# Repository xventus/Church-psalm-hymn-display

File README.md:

# Church psalm hymn display, display unit

Project for displaying hymn numbers and lyrics. This is the latest version and cheaper variant of the original FPGA VGA version. Solution based on a VGA LCD display and a remote keyboard with wireless / wired connection. Here are the complete resources including schematics and links to the modules. 

The old types of displays based on LED displays are compatible, the transmission protocol has not changed. 

# Číselník a zpěvník do kostelů

Jde o inovaci původní verze číselníku s LED i FPGA VGA zobrazovači. Protokol je zpětně kompatibilní. 
Zobrazovač je založen na VGA LCD monitoru a vzdáleného ovladače. Projekt je koncipován tak, aby jej byl schopen kdokoliv replikovat za pomocí dostupných modulů Arduino / ESP32 a nemusel vytvářet vlastní DPS.

VGA zobrazovač je založen na ESP32, konkretně levném modulu LILYGO® TTGO VGA32 V1.4  (s SD kartou)
http://www.lilygo.cn/prod_view.aspx?TypeId=50033&Id=1083

Klávesnici lze připojit buď lokálně přímo k TTGO VGA32 (PS/2), nebo přes vzdáleně přes RF modul, popřípadě RS485.
RF/RS modul se připojuje na PS/2 Mouse konektor Data (27).  

Vzdálená klávesnice je založena na ATMEGA328 v základním zapojení s 16MHz krystalem. Schéma a PCB design přiložen. Popřípadě lze použít jakékoliv Arduino. 
Oproti původní verzi nepoužívá modul MAX3421, ale využívá možnosti některých USB klávesnic pracovat v režimu PS/2. Pro zobrazení zadávaného čísla se používá modul LED displeje založený na TM1637. Pro bezdrátovou komunikaci lze využít modul APC 220. 

Kompatibilní klávesnice např. CONNECT IT NumCALC CKB-0060-BK
Nekompatibilní např. Genius NumPad i110

# Data pro SD kartu

Adresář scripts obsahuje pomocné programy pro převod žalmů a kancionálu do formátu pro VGA displej. 
Data z kancinálu byla získána stažením obsahu webu www.kancional.cz a převodem z html do vlastních dat. 
Texty žalmů jsou opisem z příšlušných knih. 

# Režimy zobrazení

V základním režimu zobrazovač nahrazuje tříciferný zobrazovač (000-996) s možností zobrazení slok (1-9).
Pokud má ESPšě modul připojenou SD kartu, lze zobrazovat žalmy, popřípadě i texty z kancionálu. 

Nastavemní viz. /doc/user-manual-csy.pdf 

# Licence

Volně k použití pro kostely, nekomerční účely ...

# Pár obrázků

# Nastavení knihoven
```
Platform espressif32 @ 6.0.1 (required: espressif32)
├── framework-arduinoespressif32 @ 3.20006.221224 (required: platformio/framework-arduinoespressif32 @ ~3.20006.0)
├── tool-esptoolpy @ 1.40400.0 (required: platformio/tool-esptoolpy @ ~1.40400.0)
├── tool-mkfatfs @ 2.0.1 (required: platformio/tool-mkfatfs @ ~2.0.0)
├── tool-mklittlefs @ 1.203.210628 (required: platformio/tool-mklittlefs @ ~1.203.0)
├── tool-mkspiffs @ 2.230.0 (required: platformio/tool-mkspiffs @ ~2.230.0)
├── tool-openocd-esp32 @ 2.1100.20220706 (required: platformio/tool-openocd-esp32 @ ~2.1100.0)
└── toolchain-xtensa-esp32 @ 8.4.0+2021r2-patch5 (required: espressif/toolchain-xtensa-esp32 @ 8.4.0+2021r2-patch5)

Libraries
└── FabGL @ 1.0.9 (required: fdivitto/FabGL @ ^1.0.9)
```

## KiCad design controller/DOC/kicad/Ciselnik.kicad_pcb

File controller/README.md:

# controller

Remote control for the display. The controller is based on atmega328p. For its operation it requires a connected numeric keypad, which communicates via PS/2 and is connected to USB. Not all USB numeric keyboards can communicate this way. 

The DOC directory contains the schematic and STL for the box. 

Other libraries are used:

SevenSegmentTM1637 - see lib/SevenSegmentTM1637 for link and description.

PS2KeyAdvanced - see lib/PS2KeyAdvanced for link and description

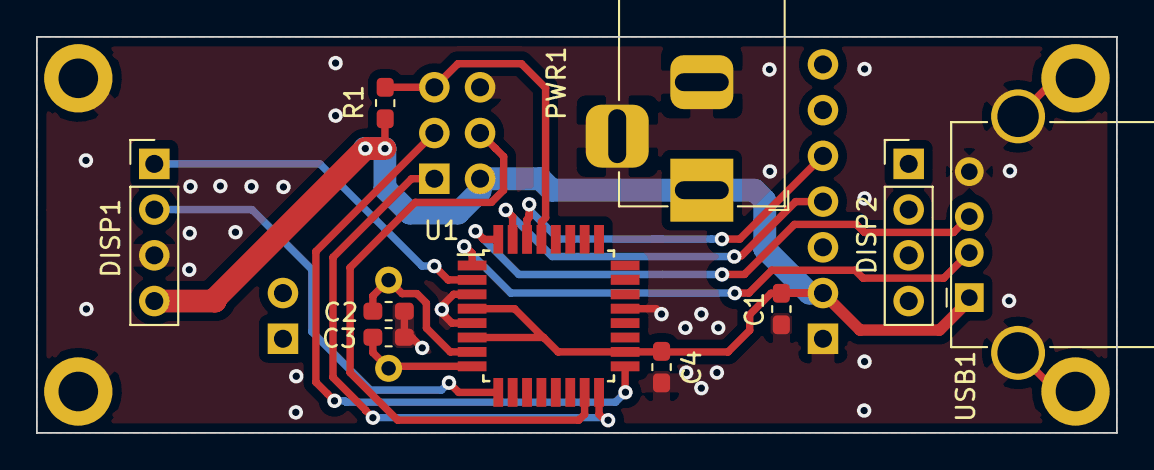
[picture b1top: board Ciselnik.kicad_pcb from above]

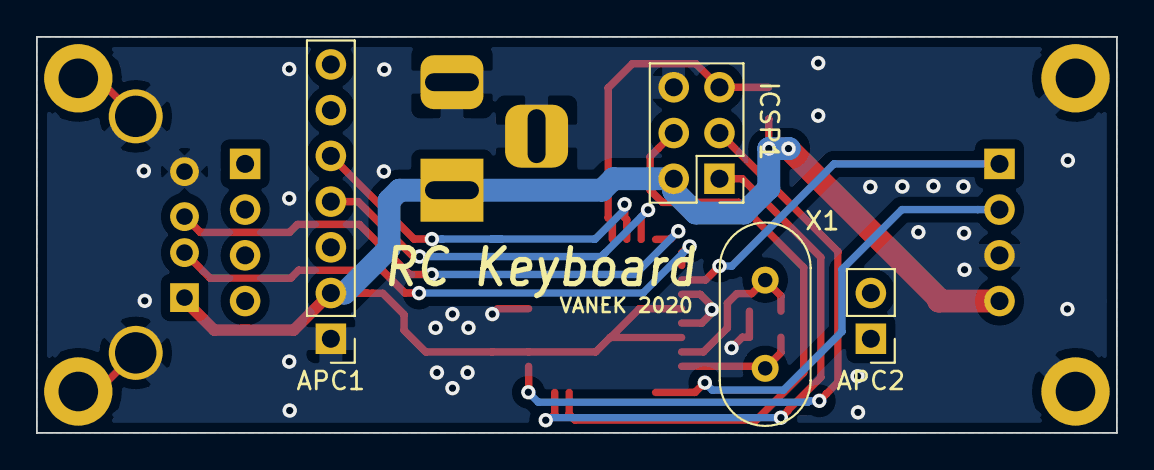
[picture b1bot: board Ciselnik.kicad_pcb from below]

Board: 2 copper layers, 60.0 x 22.0 mm, 18 parts (4 on the bottom side), 14 nets.

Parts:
APC1: APC_module; PinHeader_1x07_P2.54mm_Vertical
APC2: APC_module2; PinHeader_1x02_P2.54mm_Vertical
C1, C4: 10n; C_0603_1608Metric_Pad1.05x0.95mm_HandSolder
C2, C3: 22p; C_0603_1608Metric_Pad1.05x0.95mm_HandSolder
DISP1: DISP1_1; PinHeader_1x04_P2.54mm_Vertical
DISP2: DISP1_2; PinHeader_1x04_P2.54mm_Vertical
H1, H2, H3, H4: MountingHole_Pad; MountingHole_2.2mm_M2_DIN965_Pad
ICSP1: ICSP; PinHeader_2x03_P2.54mm_Vertical
PWR1: DC IN; BarrelJack_Horizontal
R1: 10k; R_0603_1608Metric_Pad1.05x0.95mm_HandSolder
U1: ATmega328P-AU; TQFP-32_7x7mm_P0.8mm
USB1: USB_A; USB_A_Stewart_SS-52100-001_Horizontal
X1: 16MHz; Crystal_HC18-U_Vertical

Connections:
APC_RXD: APC1.4, U1.31
APC_TXD: APC1.5, U1.30
DISP_CLK: DISP1.1, U1.2
DISP_D: DISP1.2, U1.9
GNDD: APC1.1, C1.1, C2.2, C3.2, C4.1, DISP1.3, H1.1, H2.1, H3.1, H4.1, ICSP1.6, PWR1.2, PWR1.3, U1.3, U1.5, U1.21, USB1.4, USB1.5
MISO: ICSP1.1, U1.16
MOSI: ICSP1.4, U1.15
RST: ICSP1.5, R1.1, U1.29
SCK: ICSP1.3, U1.17
USB_D+: U1.32, USB1.3
USB_D-: U1.1, USB1.2
VDD: APC1.2, C1.2, C4.2, DISP1.4, ICSP1.2, PWR1.1, R1.2, U1.4, U1.6, U1.18, USB1.1
Xtal1: C2.1, U1.7, X1.2
Xtal2: C3.1, U1.8, X1.1

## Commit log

2022-02-24 free version - VGA ESP32 based
    VGA version
2022-02-24 some photos
2022-02-24 changed default programmer to USBASP for controller
2022-02-24 case for keyboard & controller
2023-02-11 update fdivitto/FabGL@^1.0.9 and switch color from red to white
2023-02-11 Speeding up SD card loading, with the new ESP SDK, when the original code caused very slow loading.
2026-03-28 new version SD card content
